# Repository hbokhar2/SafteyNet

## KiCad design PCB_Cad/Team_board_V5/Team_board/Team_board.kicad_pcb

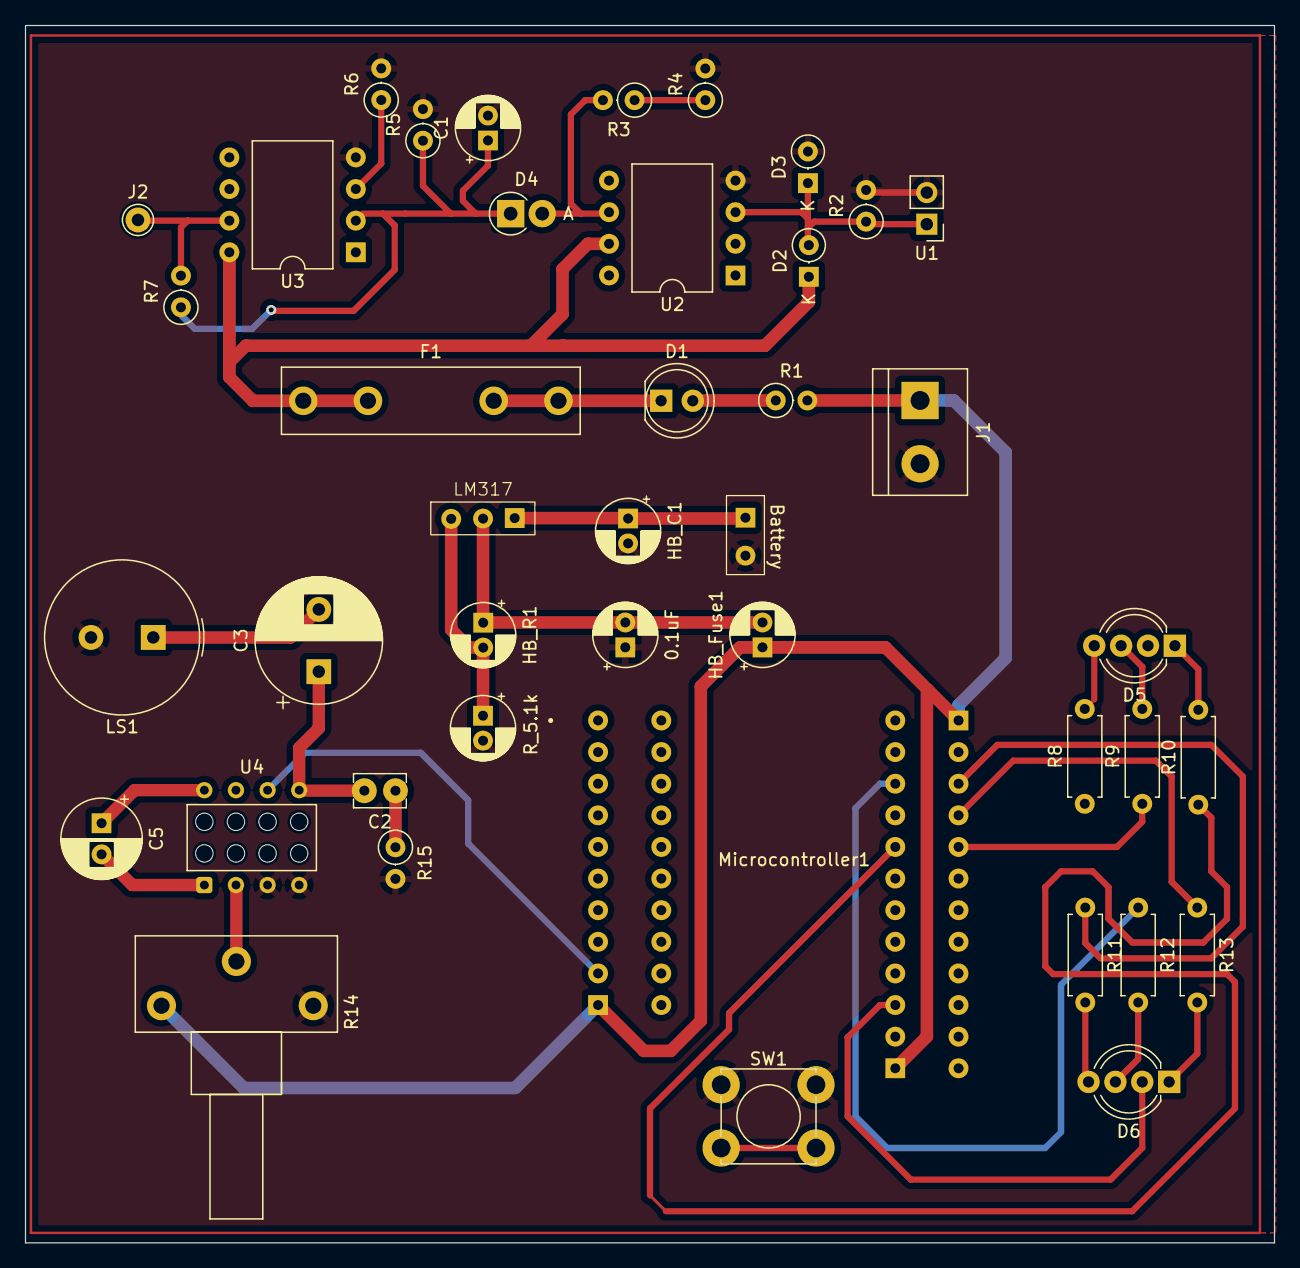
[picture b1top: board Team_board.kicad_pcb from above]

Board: 2 copper layers, 100.3 x 97.8 mm, 42 parts (0 on the bottom side), 29 nets.

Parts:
Battery1: 9v; 9V_Battery_Jumper
C1: 100uF; CP_Radial_D5.0mm_P2.00mm
C2: 22pF; C_Rect_L4.0mm_W2.5mm_P2.50mm
C3: 220uF; CP_Radial_D10.0mm_P5.00mm
C5: 10uF; CP_Radial_D6.3mm_P2.50mm
D1: LED; LED_D5.0mm
D2, D3: 5.1; D_DO-35_SOD27_P2.54mm_Vertical_KathodeUp
D4: D; D_DO-41_SOD81_P2.54mm_Vertical_AnodeUp
D5, D6: LED_ABGR; LED_D5.0mm-4_RGB_Wide_Pins
F1: Fuse; Fuseholder_Littelfuse_445_030_series_5x20mm
HB_C1, HB_C2: 0.1uF; CP_Radial_D5.0mm_P2.00mm
HB_Fuse1: 800mA; CP_Radial_D5.0mm_P2.00mm
HB_R1: 2k; CP_Radial_D5.0mm_P2.00mm
HB_R2: 5.1k; CP_Radial_D5.0mm_P2.00mm
J1: Conn_01x02_Pin; TerminalBlock_bornier-2_P5.08mm
J2: Conn_01x01_Pin; Pin_D1.0mm_L10.0mm
LM317: LM317
LS1: Speaker_Crystal; Buzzer_TDK_PS1240P02BT_D12.2mm_H6.5mm
Microcontroller1: OST_302-S241
R1, R7: 1K; R_Axial_DIN0207_L6.3mm_D2.5mm_P2.54mm_Vertical
R2: 1M; R_Axial_DIN0207_L6.3mm_D2.5mm_P2.54mm_Vertical
R3: 20k; R_Axial_DIN0207_L6.3mm_D2.5mm_P2.54mm_Vertical
R4, R5, R15: 10k; R_Axial_DIN0207_L6.3mm_D2.5mm_P2.54mm_Vertical
R6: 18k; R_Axial_DIN0207_L6.3mm_D2.5mm_P2.54mm_Vertical
R8, R9, R10, R11, R12, R13: 370; R_Axial_DIN0207_L6.3mm_D2.5mm_P7.62mm_Horizontal
R14: 10k; Potentiometer_Piher_T-16H_Single_Horizontal
SW1: SW_Push; SW_Tactile_Straight_KSA0Axx1LFTR
U1: PinHeader_1x02_P2.54mm_Vertical
U2: TL071; DIP-8_W10.16mm
U3: LM311; DIP-8_W10.16mm
U4: LM386; Samtec_HLE-104-02-xx-DV-PE_2x04_P2.54mm_Horizontal

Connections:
+5V: D1.1 (K), D1.2 (A), D2.1 (K), F1.1, F1.2, HB_Fuse1.1, J1.1, Microcontroller1.2, Microcontroller1.23, R1.1, R1.2, R14.1, U2.7 (V+), U3.8 (V+)
Earth: Battery1.2 (-), C1.2, D3.2 (A), HB_C1.2, HB_C2.1, HB_R2.2, J1.2, LS1.2, R2.2, R4.2, R5.2, R6.2, R14.3, R15.2, SW1.1, U1.2 (-), U2.4 (V-), U3.4 (V-), U4.3 (+), U4.4 (GND)
unnamed: Battery1.1 (+), HB_C1.1, LM317.3 (Input)
unnamed: C2.1, C3.1, U4.5
unnamed: C2.2, R15.1
unnamed: C3.2, LS1.1
unnamed: C5.1, U4.1 (GAIN)
unnamed: C5.2, U4.8 (GAIN)
unnamed: D2.2 (A), D3.1 (K), R2.1, U1.1 (+), U2.3 (+)
unnamed: D4.2 (A), R3.2, U2.6
unnamed: C1.1, D4.1 (K), R5.1, R7.1, U3.2 (+)
unnamed: D5.2 (BK), R10.2
unnamed: D5.3 (GK), R9.2
unnamed: D5.4 (RK), R8.2
unnamed: D6.2 (BK), R13.2
unnamed: D6.3 (GK), R12.2
unnamed: D6.4 (RK), R11.2
unnamed: HB_R1.2, HB_R2.1, LM317.1 (Adjust)
unnamed: HB_C2.2, HB_Fuse1.2, HB_R1.1, LM317.2 (Output)
unnamed: R3.1, R4.1, U2.2 (-)
unnamed: R6.1, U3.3 (-)
unnamed: R14.2, U4.2 (-)
P0.1: J2.1, R7.2, U3.7
Pin 2.2: D6.1 (A), Microcontroller1.19
Pin 3.0: Microcontroller1.9, R10.1
Pin 3.1: Microcontroller1.10, R9.1
Pin 3.3: Microcontroller1.8, R13.1
Pin 3.4: Microcontroller1.5, R12.1
Pin 3.5: Microcontroller1.6, R11.1

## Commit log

2024-07-28 Final
2024-07-28 Path Update
2024-07-28 Update_2
